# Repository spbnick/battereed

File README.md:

Battereed
=========

Battereed is a battery adapter with a reed switch. It's useful for controlling
battery-powered devices which don't have a switch of their own, like car key
fobs. Put a CR1620 battery inside, and then you can put it in place of a
CR2032 battery. After that you can control the device's power with a magnet,
which could be embedded into [a mechanical switch][kona-key-switch].

[kona-key-switch]: https://github.com/spbnick/kona-key-switch

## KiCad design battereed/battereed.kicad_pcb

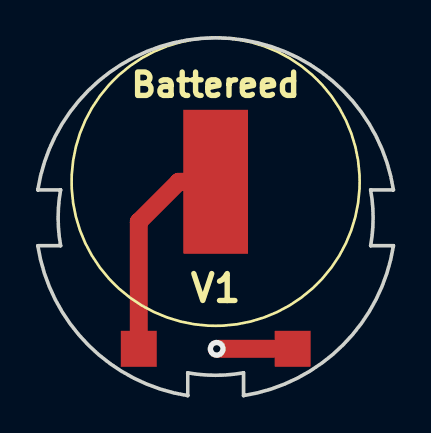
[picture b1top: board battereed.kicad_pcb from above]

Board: 2 copper layers, 19.8 x 19.9 mm, 3 parts (1 on the bottom side), 2 nets.

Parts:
J1: CR16XX_minus
J2: CR20XX_minus
SW1: SW_Reed; CT05-1535-G1

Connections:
unnamed: J1.1, SW1.1
unnamed: J2.1, SW1.2

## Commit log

2019-05-30 First working but wrong-sized board
2019-06-06 Rename mockup to model
2019-06-06 Increase model soldering error
2019-06-21 Add README.md
